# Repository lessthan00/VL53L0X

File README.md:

# VL53L0X  

参考设计:https://e.tb.cn/h.6H1u5hUDzXThlKt?tk=nUvbVjZAV5J  
红外测距模块  
完全集成的微型模块  
940 nm激光器VCSEL  
VCSEL驱动器  
测距传感器，内嵌高级微控制器  
4.4 x 2.4 x 1.0 mm  
快速、精确测距  
测量的绝对距离可达2 m  
报告的距离与目标反射率无关  
先进的嵌入式光学串扰补偿，简化盖片的选择  
人眼安全  
1类激光器件，符合最新标准IEC 60825-1:2014（第3版）要求  
可轻松集成  
单回流焊元件  
无附加光学元件  
单电源  
用于器件控制和数据传输的I2C接口  
Xshutdown（复位）和中断GPIO  
可编程I2C地址 address 0x52  
接口定义1 VIN GND SCL SDA  
接口定义2 VIN GND SCL SDA GPIO1 XSHUT  
  
封装  LGA12(4.4x2.4x1mm) 可以焊接  
V 2.6~3.5V  
波段940nm红外  
芯片价格约5元.  
  
[datasheet](https://www.st.com.cn/zh/imaging-and-photonics-solutions/vl53l0x.html)  
  
XSHUT 低电平复位  
GPIO1 中断开漏输出  
电容靠近 ADDVCSEL和AVSSVSEL引脚  
  
需要注意焊接温度曲线.

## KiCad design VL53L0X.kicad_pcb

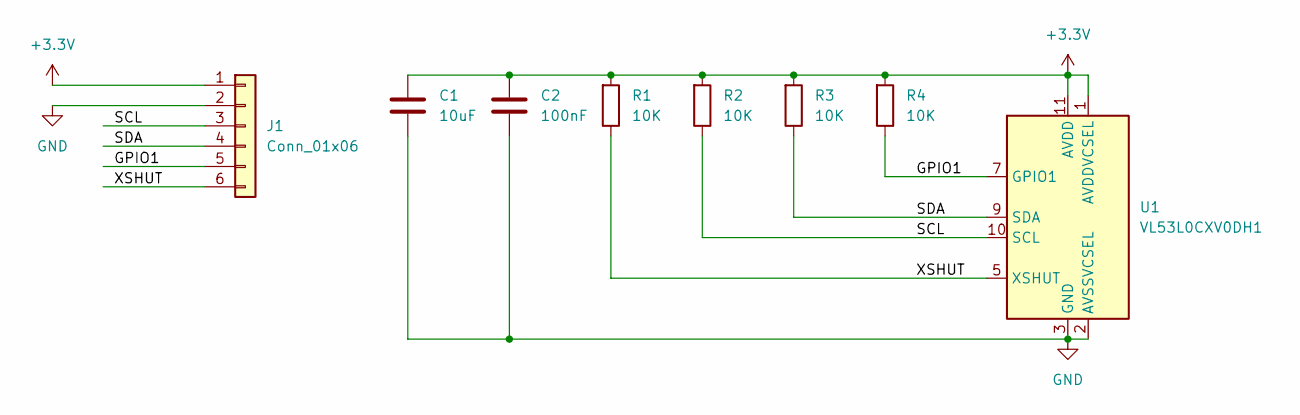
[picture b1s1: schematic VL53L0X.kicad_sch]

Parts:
C1: 10uF; C_1206_3216Metric
C2: 100nF; C_1206_3216Metric
J1: Conn_01x06; PinHeader_1x06_P2.54mm_Vertical
R1, R2, R3, R4: 10K; R_1206_3216Metric
U1: VL53L0CXV0DH1; ST_VL53L1x

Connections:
+3.3V: C1.1, C2.1, J1.1, R1.1, R2.1, R3.1, R4.1, U1.1 (AVDDVCSEL), U1.11 (AVDD)
/GPIO1: J1.5, R4.2, U1.7 (GPIO1)
/SCL: J1.3, R2.2, U1.10 (SCL)
/SDA: J1.4, R3.2, U1.9 (SDA)
/XSHUT: J1.6, R1.2, U1.5 (XSHUT)
GND: C1.2, C2.2, J1.2, U1.2 (AVSSVCSEL), U1.3 (GND), U1.4 (GND), U1.6 (GND), U1.12 (GND)

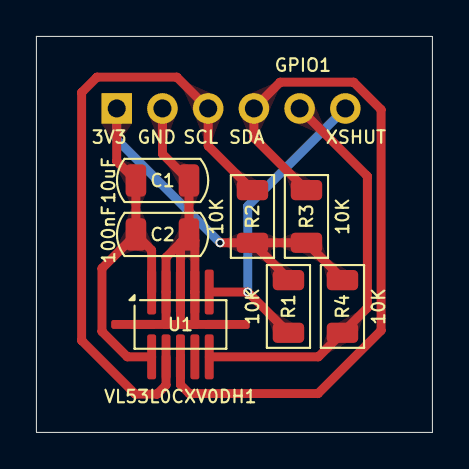
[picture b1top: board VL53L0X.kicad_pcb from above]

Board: 2 copper layers, 22.0 x 22.0 mm, 8 parts (1 on the bottom side), 6 nets.
